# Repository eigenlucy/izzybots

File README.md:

# izzybots

Wooohooo a new package!

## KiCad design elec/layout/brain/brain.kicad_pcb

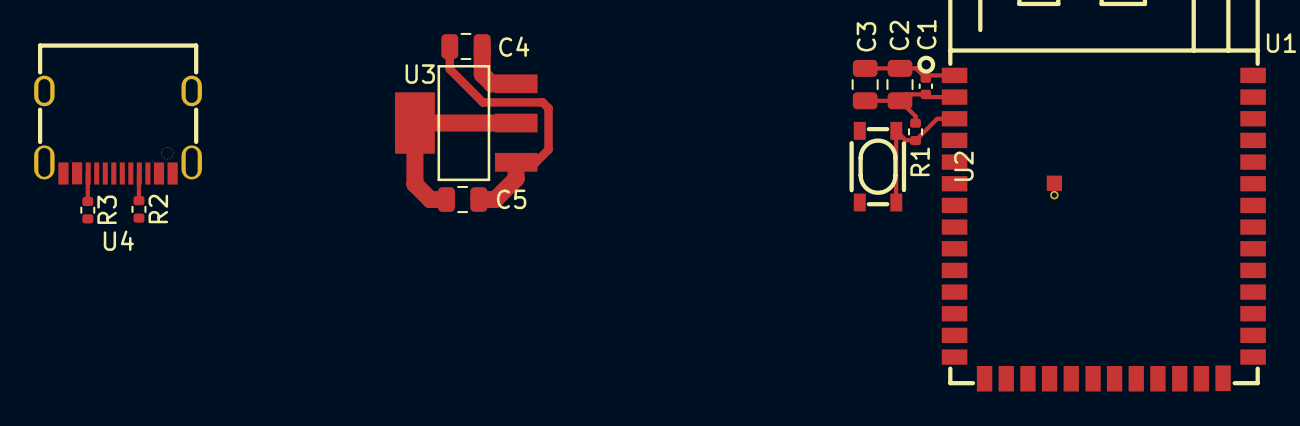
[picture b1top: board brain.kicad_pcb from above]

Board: 2 copper layers, 12 parts (0 on the bottom side), 8 nets.

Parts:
C1: 16V 100nF X7R ±10% 0402 Multilayer Ceramic Capaci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; C0402
C2, C3, C4, C5: 25V 10uF X5R ±10% 0805 Multilayer Ceramic Capacit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; C0805
R1: 62.5mW Thick Film Resistors 50V ±100ppm/℃ ±1% 10k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; R0402
R2, R3: 62.5mW Thick Film Resistors 50V ±100ppm/℃ ±1% 4.7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; R0402
U1: ?; WIRELM-SMD_ESP32-S3-WROOM-1
U2: ?; KEY-SMD_4P-L4.2-W3.2-P2.20-LS4.6
U3: ?; SOT-223-3_L6.5-W3.4-P2.30-LS7.0-BR
U4: ?; USB-C-SMD_KH-TYPE-C-16P

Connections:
cc1: R2.1, U4.A5
cc2: R3.1, U4.B5
dm: U1.13, U4.A7, U4.B7
dp: U1.14, U4.A6, U4.B6
en: R1.2, U1.3, U2.1, U2.2
gnd: C1.2, C2.2, C3.2, C4.2, C5.2, R2.2, R3.2, U1.1, U1.40, U1.41, U2.3, U2.4, U3.1, U4.1, U4.2, U4.3, U4.4, U4.A1, U4.A12, U4.B1, U4.B12
vcc: C1.1, C2.1, C3.1, C5.1, R1.1, U1.2, U3.2, U3.4
vcc-1: C4.1, U3.3, U4.A4, U4.A9, U4.B4, U4.B9

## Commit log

2024-12-20 Configure project
